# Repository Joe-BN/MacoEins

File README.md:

# MacroEins

Easy to assemble, customize and improve

First iteration of the macropad project.

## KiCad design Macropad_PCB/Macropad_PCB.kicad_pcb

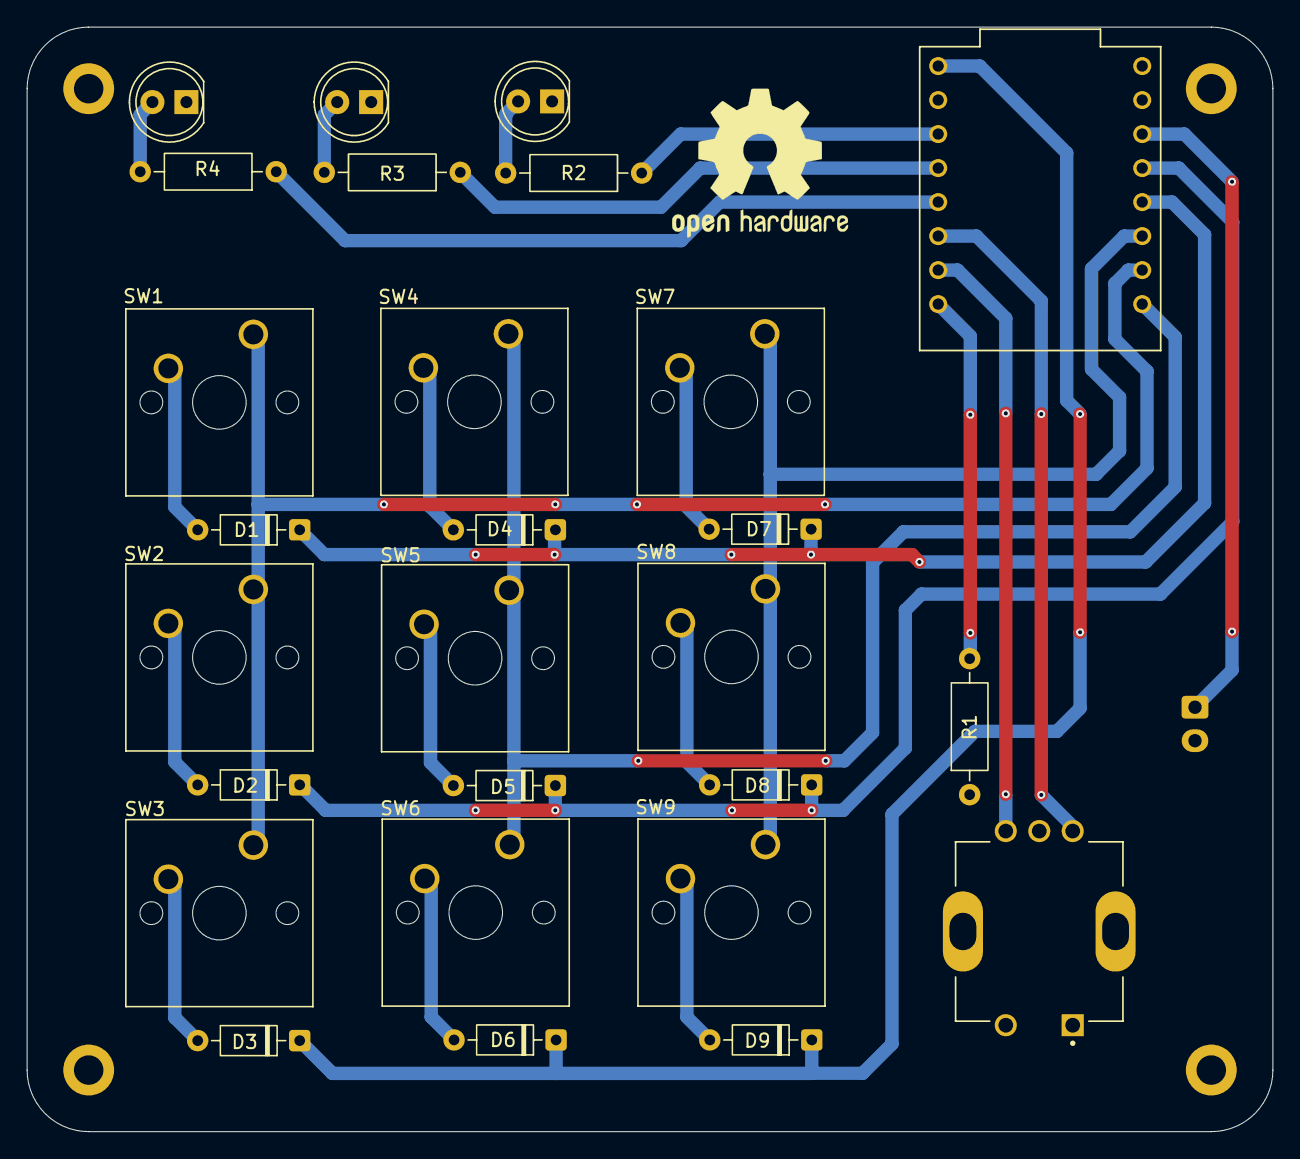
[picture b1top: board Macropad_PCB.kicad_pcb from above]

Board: 2 copper layers, 93.1 x 82.5 mm, 32 parts (1 on the bottom side), 26 nets.

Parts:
D1, D2, D3, D4, D5, D6, D7, D8, D9: D_45deg; D_DO-35_SOD27_P7.62mm_Horizontal
D10, D11, D12: LED; LED_D5.0mm
H1, H2, H3, H4: MountingHole; MountingHole_2.2mm_M2_ISO14580_Pad
J1: Battery Power connector; JST_EH_S2B-EH_1x02_P2.50mm_Horizontal
R1: 1K; R_Axial_DIN0207_L6.3mm_D2.5mm_P10.16mm_Horizontal
R2, R3, R4: 330; R_Axial_DIN0207_L6.3mm_D2.5mm_P10.16mm_Horizontal
SW1, SW2, SW3, SW4, SW5, SW6, SW7, SW8, SW9: SW_MEC_5G; JBN_SW_Cherry_MX_1.00u_PCB
SW10: RotaryEncoder; XDCR_PEC11R-4020F-S0024
U1: ESP32-C3_SUPERMINI_TH; MODULE_ESP32-C3_SUPERMINI_TH

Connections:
GND: D10.1 (K), D11.1 (K), D12.1 (K), J1.2, R1.1, SW10.C, U1.G (GND)
LED_00: R2.1, U1.7 (GPIO7)
LED_01: R3.1, U1.8 (GPIO8)
LED_02: R4.1, U1.9 (GPIO9)
unnamed: D1.2 (A), SW1.3 (B)
unnamed: D2.2 (A), SW2.3 (B)
unnamed: D3.2 (A), SW3.3 (B)
unnamed: D4.2 (A), SW4.3 (B)
unnamed: D5.2 (A), SW5.3 (B)
unnamed: D6.2 (A), SW6.3 (B)
unnamed: D7.2 (A), SW7.3 (B)
unnamed: D8.2 (A), SW8.3 (B)
unnamed: D9.2 (A), SW9.3 (B)
unnamed: D10.2 (A), R2.2
unnamed: D11.2 (A), R3.2
unnamed: D12.2 (A), R4.2
bat +: J1.1, U1.3.3 (3V3)
col_00: SW1.1 (A), SW2.1 (A), SW3.1 (A), U1.1 (GPIO1)
col_01: SW4.1 (A), SW5.1 (A), SW6.1 (A), U1.0 (GPIO0)
col_02: SW7.1 (A), SW8.1 (A), SW9.1 (A), U1.2 (GPIO2)
encoder_sw: R1.2, U1.21 (GPIO21)
rotary_A: SW10.A, U1.10 (GPIO10)
rotary_B: SW10.B, U1.20 (GPIO20)
row_00: D1.1 (K), D4.1 (K), D7.1 (K), U1.3 (GPIO3)
row_01: D2.1 (K), D5.1 (K), D8.1 (K), U1.4 (GPIO4)
row_02: D3.1 (K), D6.1 (K), D9.1 (K), U1.5 (GPIO5)
